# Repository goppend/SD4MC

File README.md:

# SD4MC
An SD2SIO clone using (currently) available parts. A weekend project to keep myself busy while I'm waiting for parts and boards to arrive. :)

The SD2SIO/MX4SIO is an adapter for the Playstation 2, allowing the use of removable micro SD card in lieu of a memory card.
It allows applications or backups to be ran on softmodded PS2 hardware, so a Free MC Boot memory card is required.

To learn more about the history of this project and how to use it, discussion threads are on [psx-place.com](https://www.psx-place.com/threads/sio2sd-sd-card-adapter-and-sd-driver-for-the-ps2-sio2-interface.29210/), [trisaster.de](https://psxtools.de/index.php/Thread/81784-Ein-SD-Adapter-f%C3%BCr-den-MemoryCard-Anschluss-der-PS2/), and [psx-tools.de](http://www.trisaster.de/forum/index.php?topic=8324.0).

Thanks to Takeshi and many others at psx-place.com for the initial design and inspiration to create this.

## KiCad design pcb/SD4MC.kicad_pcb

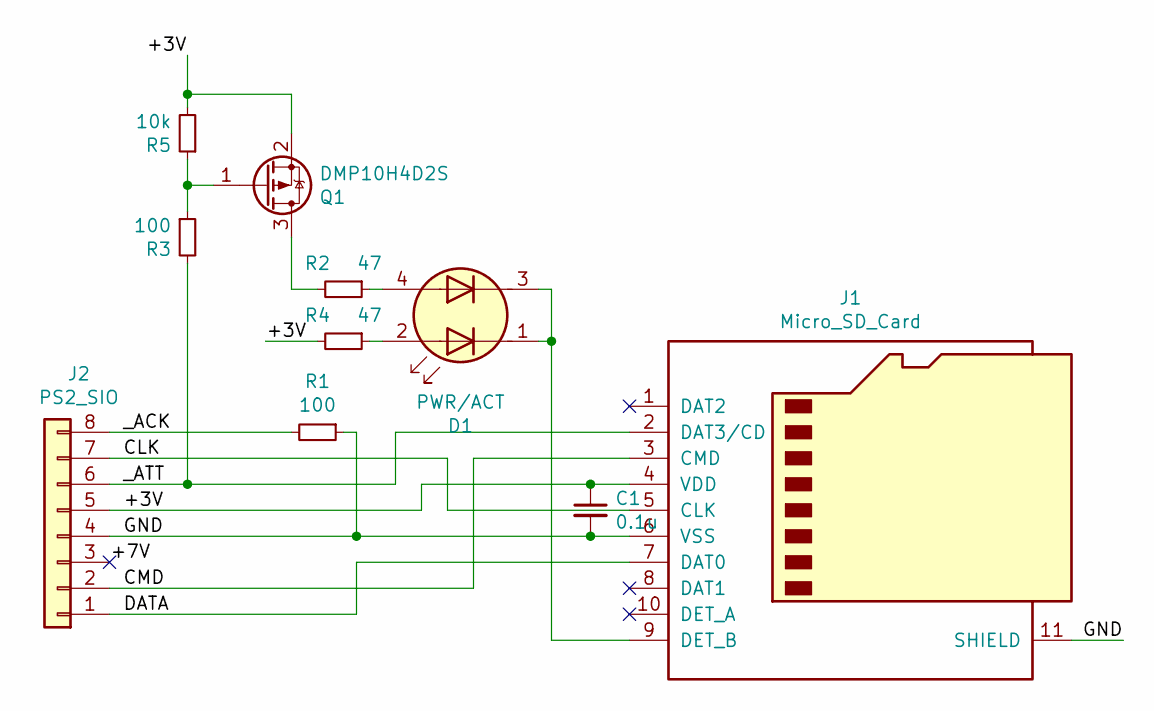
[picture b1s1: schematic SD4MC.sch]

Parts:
C1: 0.1u; C_0805_HandSoldering
D1: PWR/ACT; Dialight_Dual_LED_5977703607F
J1: Micro_SD_Card; Yamaichi_microsd_PJS008-2003-1
J2: PS2_SIO; PlayStation2_MemoryCard; Digikey N/A
Q1: DMP10H4D2S; SOT-23
R1, R3: 100; R_0805_HandSoldering
R2, R4: 47; R_0805_HandSoldering
R5: 10k; R_0805_HandSoldering

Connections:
/+3V: C1.1, J1.4 (VDD), J2.5, Q1.2 (S), R4.2, R5.2
/+7V: J2.3
/CLK: J1.5 (CLK), J2.7
/CMD: J1.3 (CMD), J2.2
/DATA: J1.7 (DAT0), J2.1
/GND: C1.2, J1.6 (VSS), J1.11 (SHIELD), J2.4, R1.1
/_ACK: J2.8, R1.2
/_ATT: J1.2 (DAT3/CD), J2.6, R3.2
unnamed: D1.1 (A1), D1.3 (A2), J1.9 (DET_B)
unnamed: D1.2 (K1), R4.1
unnamed: D1.4 (K2), R2.1
unnamed: Q1.1 (G), R3.1, R5.1
unnamed: Q1.3 (D), R2.2

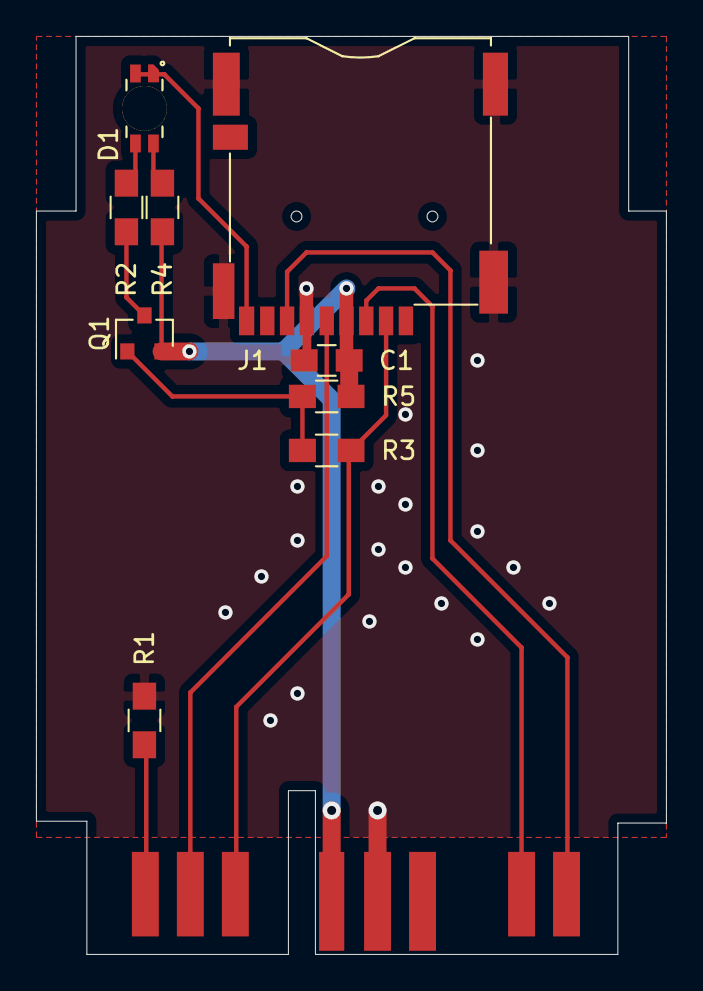
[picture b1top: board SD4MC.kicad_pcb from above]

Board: 2 copper layers, 35.0 x 51.0 mm, 10 parts (0 on the bottom side), 12 nets.

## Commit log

2022-02-14 Initial commit - v0.1
